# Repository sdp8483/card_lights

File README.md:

# Greeting Card LEDs

**NOTE** This project is in progress and info may change. More details will be added soon

Add LEDs to your greeting cards. A simple touch of the back side of the device turns on the LEDs. Touch again to turn the LEDs off. A 60 second auto off feature will turn off the LEDs for you when left on to extend battery life.

## Installation

Position the LEDs and PCB on your card in whatever orientation you would like. Avoid bending the LED wires at sharp angles or too many times as the wire will fatigue and break. The back side of the PCB is touch sensitive (the side labeled touch) but may not be the same sensitivity over the entire back. Touch different areas to determine the most sensitive area and position that on your card where you would like the recipient to touch to turn on the LEDs. Attache the PCB using double sided tape or another method of your choosing that will firmly attache it to the greeting card. The LEDs can also be taped down or affixed however you would like.

After installing remove the battery and wait for 30 seconds before reinstalling the battery. Try not to turn on the LEDs while installing the battery. Do not turn on the LEDs for about 60 seconds. During this time the touch controller is calibrating to ensure that it recognizes your finger tip when you touch it.

## Tips and Tricks

### Don't need so many LEDs? 
You can cut them off near the PCB using scissors (probably best to use an pair you don't care about) or wire cutters.

### Increasing Touch Sensitivity
If you find the LEDs do not light up when you touch the back of the PCB you can increase the sensitivity of the touch controller by cutting the jumper JP2. 
TODO: add photos and more

### Adding your own Touch Pad
To add your own touch pad to for example make the whole front of the greeting card touch sensitive cut JP4 and then add solder to bridge JP3. Solder a connection to your new touch pad to the square pad at the bottom of the PCB. You can directly connect the the new touch pad or use wire. Copper tape works great to make a new touch pad. For a lower cost option aluminum foil will also work. Attach it to the greeting card using double sided tape. Tape can be used to attach a wire from the PCB to the aluminum touch pad. TODO: photos

### Ghosts
Does the LEDs appear to turn on without anyone touching them? While we cannot rule out ghosts it is most likely the touch controller being super sensitive. Remove the battery for at least a minute and then reinstall the battery while trying not to trigger the LEDs. Don't touch the PCB for a few  minutes. If that does not solve the problem try changing the battery for a new one. A battery near the end of its light maybe causing the touch controller to act up. If all else fails treat is as a feature and not a bug. The touch controller maybe acting up in your specific situation due to a number of reasons such as the paper material nearby, other items nearby, electrical interference, and more.

## Directory Outline
- [`~/pcb/`](pcb) is for KiCAD design files. Inside is the touch PCB design along with a simple PCB design. The simple PCB design uses a tactile button to turn on the LEDs when held down. It was a prototype and is left in this repository just incase it is needed again. Both designs are single sided (if you don't count the touch pad) and can be easily manufactured at home using a PCB router. The POGO programmer PCB design files are for makeing a POGO board to program the ATTINY10 in circuit. You will need additional devices to program the ATTINY10 in HV mode. Details to be added at a later date.
- [`~/firmware/`](firmware) is for firmware souce code and binaries for the touch PCB. If you want to write you own code start here.
- [`~/enclosure/`](enclosure) is for the POGO programmer and is a holder.

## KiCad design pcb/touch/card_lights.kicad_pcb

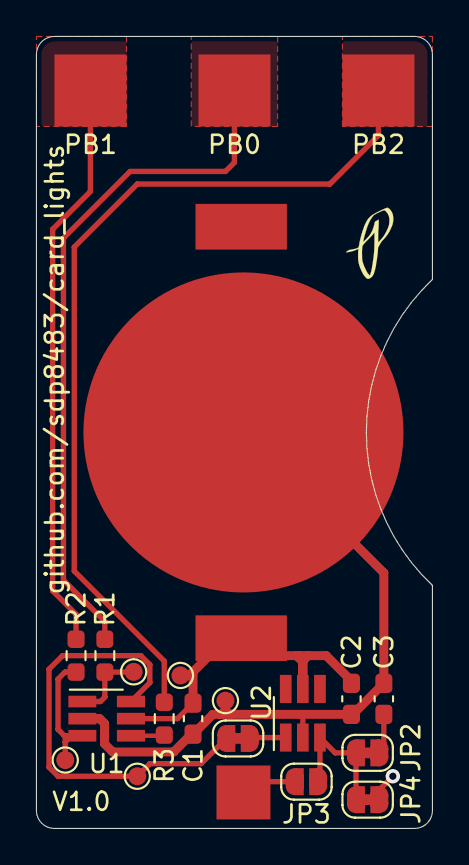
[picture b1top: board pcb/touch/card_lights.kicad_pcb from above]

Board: 2 copper layers, 22.0 x 44.0 mm, 22 parts (0 on the bottom side), 13 nets.

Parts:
BT1: Battery_Cell; BAT-HLD-001
C1, C2: 100n; C_0603_1608Metric_Pad1.08x0.95mm_HandSolder
C3: 10p; C_0603_1608Metric_Pad1.08x0.95mm_HandSolder
J2, J3, J4: LED_PAD; TestPoint_Pad_4.0x4.0mm
JP1, JP2, JP4: Jumper_NC_Small; SolderJumper-2_P1.3mm_Bridged_RoundedPad1.0x1.5mm
JP3: Jumper_NC_Small; SolderJumper-2_P1.3mm_Open_RoundedPad1.0x1.5mm
R1, R2, R3: 91; R_0603_1608Metric_Pad0.98x0.95mm_HandSolder
TP1, TP2, TP3, TP4, TP5: TestPoint; TestPoint_Pad_D1.0mm
TP6: TestPoint; TestPoint_Pad_3.0x3.0mm
U1: ATtiny10-TS; SOT-23-6_Handsoldering
U2: TTP223E-HA6; SOT-23-6_Handsoldering

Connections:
+3V0: BT1.1, C1.2, C2.2, TP1.1, U1.5, U2.5
/PB0: R1.2, TP2.1, U1.1
/PB1: R2.2, TP3.1, U1.3
/PB2: R3.2, U1.4
/PB3: JP1.1, TP4.1, U1.6
/TOUCH: JP2.1, JP3.1, JP4.1, U2.3
GND: BT1.2, C1.1, C2.1, C3.2, TP5.1, U1.2, U2.2
unnamed: C3.1, JP2.2
unnamed: J2.1, R1.1
unnamed: J3.1, R2.1
unnamed: J4.1, R3.1
unnamed: JP1.2, U2.1
unnamed: JP3.2, TP6.1

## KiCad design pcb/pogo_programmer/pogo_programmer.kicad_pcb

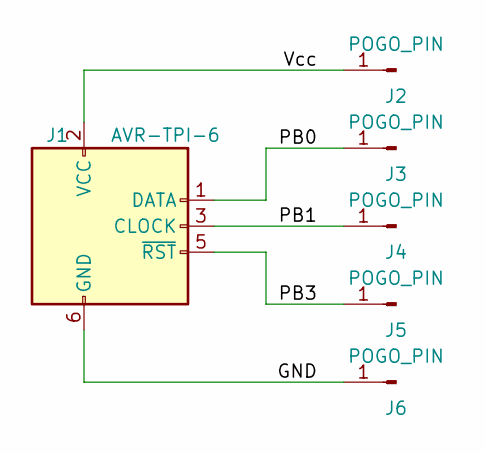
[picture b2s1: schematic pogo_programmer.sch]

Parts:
J1: AVR-TPI-6; PinHeader_2x03_P2.54mm_Vertical
J2, J3, J4, J5, J6: POGO_PIN; pl_pogo_D1mm

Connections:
/GND: J1.6 (GND), J6.1
/PB0: J1.1 (DATA), J3.1
/PB1: J1.3 (CLOCK), J4.1
/PB3: J1.5 (~RST), J5.1
/Vcc: J1.2 (VCC), J2.1

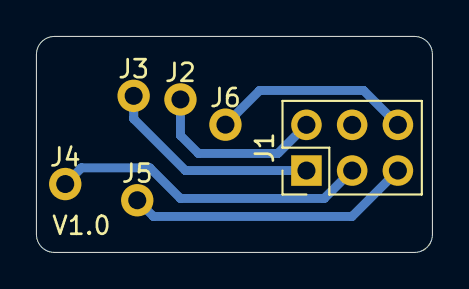
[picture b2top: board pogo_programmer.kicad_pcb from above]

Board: 2 copper layers, 22.0 x 12.0 mm, 6 parts (0 on the bottom side), 5 nets.

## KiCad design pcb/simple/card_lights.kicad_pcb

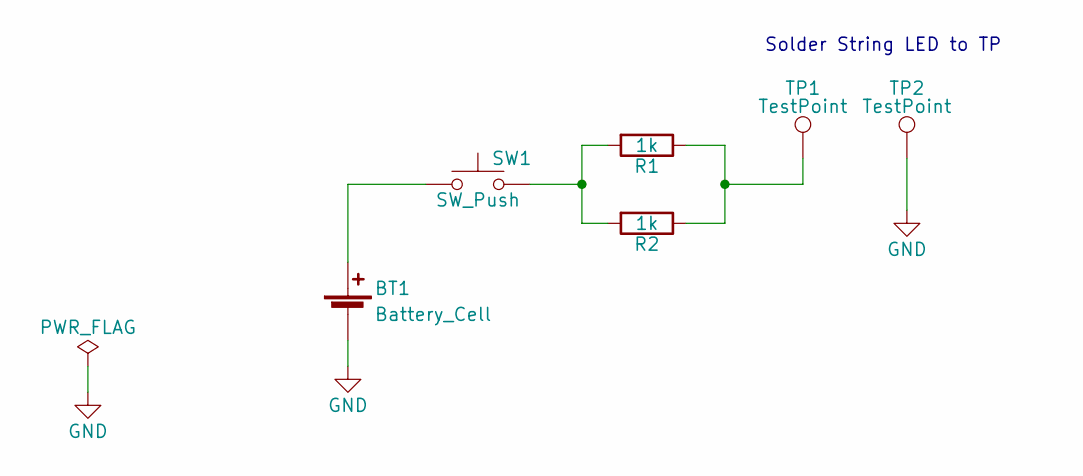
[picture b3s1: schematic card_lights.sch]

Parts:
BT1: Battery_Cell; BAT-HLD-001
R1, R2: 1k; R_0603_1608Metric_Pad0.98x0.95mm_HandSolder
SW1: SW_Push; Bright_TSA123G60-250
TP1, TP2: TestPoint; TestPoint_Pad_4.0x4.0mm

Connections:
GND: BT1.2 (-), TP2.1
unnamed: BT1.1 (+), SW1.1
unnamed: R1.1, R2.1, TP1.1
unnamed: R1.2, R2.2, SW1.2

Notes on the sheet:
Solder String LED to TP

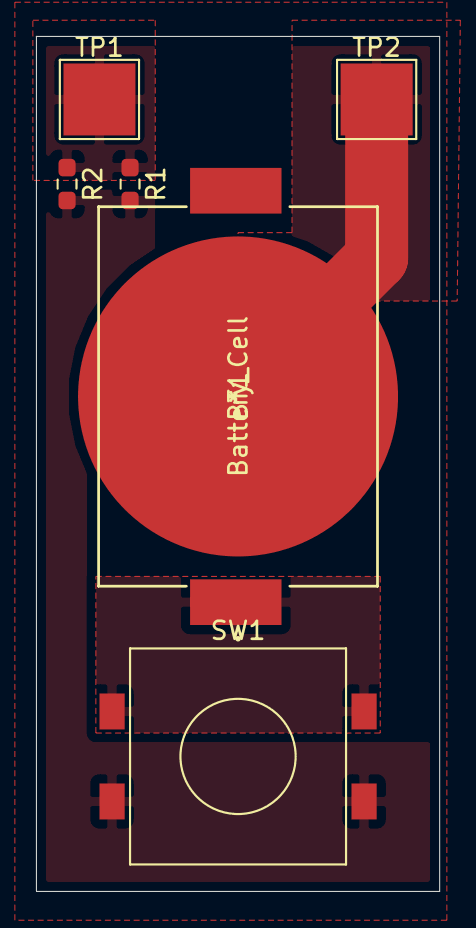
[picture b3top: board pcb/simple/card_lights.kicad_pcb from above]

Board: 2 copper layers, 22.4 x 47.5 mm, 6 parts (0 on the bottom side), 4 nets.

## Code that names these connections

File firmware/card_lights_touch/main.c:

/* Card Lights Touch Edition
 *  using external capacitive touch controller to trigger LEDs
 * 
 * Simple Conneciton Diagram
 *       ATTINY10
 *       ---------
 *   3v | 5  1 PB0| -> LED1
 *   GND| 2  3 PB1| -> LED2
 *      |    4 PB2| -> LED3
 *      |    6 PB3| -> TOUCH_INPUT
 *       ---------
 *        SOT23-6
 */


#include <avr/io.h>
#include <util/delay.h>
#include <avr/interrupt.h>
#include <avr/sleep.h>

#include "main.h"

/* Funciton Prototypes */
void initPCINT0(void);

int main (void) {
    /* setup PB0 to PB2 as outputs for LEDs */
    DDRB |= (BIT0 | BIT1 | BIT2);

    /* setup PB3 as input with internal pullup */
    //DDRB &= ~BIT3;
    //PUEB |= BIT3;

    /* interrupt on PB3 */
    initPCINT0();

    /* set sleep mode */
    set_sleep_mode(SLEEP_MODE_PWR_DOWN);

    while (1)
    {
        sleep_enable();
        sleep_cpu();        /* go to sleep */
        sleep_disable();    /* wake from sleep here */

        //cli();
        PORTB |= BIT0;      /* turn on light */
        _delay_ms(5000);
        PORTB &= !BIT0;     /* turn off light, go to sleep */
        //sei();
    }
    
}
/* initialize pin change interrupt service routine */
void initPCINT0(void) {
    PCICR |= BIT0;  /* pin change interrupt enable */
    PCMSK |= BIT3;  /* pin change interrupt on PB3/PCINT3 */
    sei();          /* set global interrupt enable bit */
}

/* pin change interrupt service routine */
ISR(PCINT0_vect){
    /*    
    if (bit_is_clear(PINB, PB3)) {
        PORTB |= BIT1;
    } else {
        PORTB &= !BIT1;
    } */
}

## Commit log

2020-11-14 init commit
2020-11-15 user larger tip for copper fill removal
2020-11-15 remove files
2020-12-19 move previous simple button pcb to seperate dir
2020-12-19 create touch PCB
2020-12-19 round corners, cutout to grab coin cell
2020-12-20 init firmware commit
2020-12-20 output gerbers
2020-12-20 remove old gcode
2020-12-20 create project gcode
2020-12-20 update gcode names
2020-12-20 firmware tweaks
2020-12-20 create ibom
2020-12-21 diable timer during sleep, no pullup
2020-12-24 seperate funcitons to files, add preprocessor stuff
2020-12-31 add touch sensitivity adjustment capacitor
2020-12-31 annotations
2020-12-31 add diode to RESET for insystem HV programming that does not damage TTP223E
2020-12-31 add test points for in system programming
2020-12-31 annotate and add footprints
2021-01-01 add new components, start making pretty for PCB manufacture
2021-01-01 define F_CPU
2021-01-01 enable trigger on low high transisiton, change schmatic to match
2021-01-01 update touch controller to not use output toggle
2021-01-01 pcb layout changes
2021-01-02 create pogo pin board
2021-01-02 create cr2032_simulator
2021-01-03 remove old fw
2021-01-15 generate ibom
2023-03-27 build

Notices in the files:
parts and their libraries:
Copyright 2016 Accelerated Designs. All rights reserved.
